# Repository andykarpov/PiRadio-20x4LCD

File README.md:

PiRadio-20x4LCD
=======

Python based internet radio project for RaspberryPi to play internet radio streams and control it using custom atmega328p-based board with 
connected 20x4 character display, rotary encoder, potentiometer, 2xMSGEQ7 board and PT2322 audio processor board.

All hardware-specific EAGLE projects are located under 'schematic' subfolder. 
All required non-standard libraries are available upon request. Some of them are self-made from scratch, some of them googled in the internet.

**Prerequesties:**

1. You should have a working raspberry pi with latest raspbian (at least 2012-12-18)
2. Also we assumes that your network connection (wired or wireless) is also running well
3. Your arduino-based board is connected via internal on-board serial port  
   (assuming arduino/PyRadioInterface sketch is already uploaded there, all external hardware is connected to the arduino - 
   such as rotary encoder, potentiometer, PT2322 board, MSGEQ7 board)
4. You are logged in as user 'pi' with it's default home at /home/pi/ 

**Installation:**

1. sudo apt-get update && sudo apt-get upgrade
2. sudo apt-get install mpd mpc python-serial python-mpd2 git
3. cd && git clone https://github.com/andykarpov/PiRadio-20x4LCD.git PiRadio
4. cd /home/pi/PiRadio
5. sudo ln -s /home/pi/PiRadio/etc/init.d/pi-radio /etc/init.d/pi-radio
6. chmod -R a+rwx data/ 
7. cd /home/pi/PiRadio/init.d/
8. sudo chmod a+x pi-radio
9. sudo nano /etc/mpd - change "localhost" to "any"
10. sudo alsamixer - set a desired output level
11. sudo alsactl store
12. sudo /etc/init.d/pi-radio start
13. sudo update-rc.d pi-radio defaults
14. sudo reboot

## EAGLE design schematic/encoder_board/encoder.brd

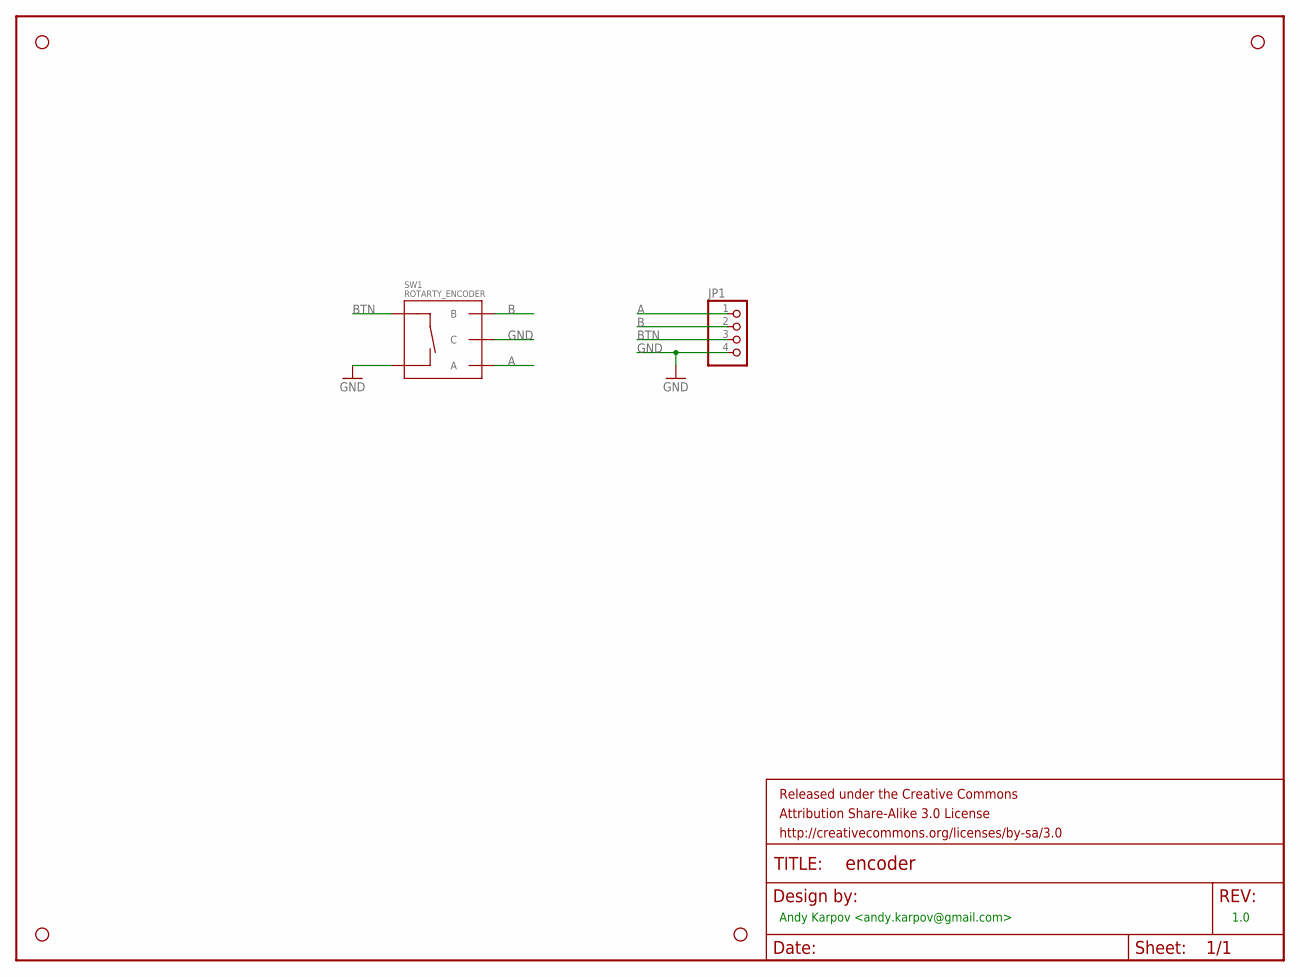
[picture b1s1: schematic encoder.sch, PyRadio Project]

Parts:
FRAME1: FRAME-LETTER; CREATIVE_COMMONS
JP1: PINHD-1X4; 1X04
STANDOFF1, STANDOFF2, STANDOFF3, STANDOFF4: STAND-OFF
SW1: ROTARTY_ENCODER; ROTARY_ENC_PLAIN

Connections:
A: JP1.1, SW1.A
B: JP1.2, SW1.B
BTN: JP1.3, SW1.SW+
GND: JP1.4, SW1.C, SW1.SW-

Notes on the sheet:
Andy Karpov <andy.karpov@gmail.com>
1.0

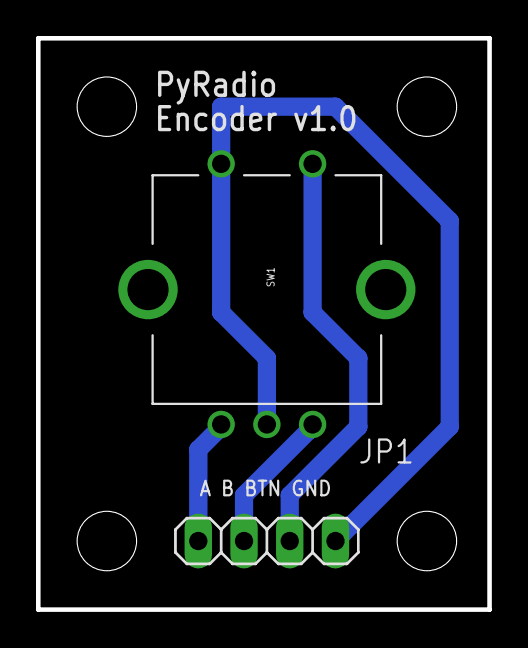
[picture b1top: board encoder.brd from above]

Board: 2 copper layers, 25.1 x 31.7 mm, 7 parts (0 on the bottom side), 4 nets.

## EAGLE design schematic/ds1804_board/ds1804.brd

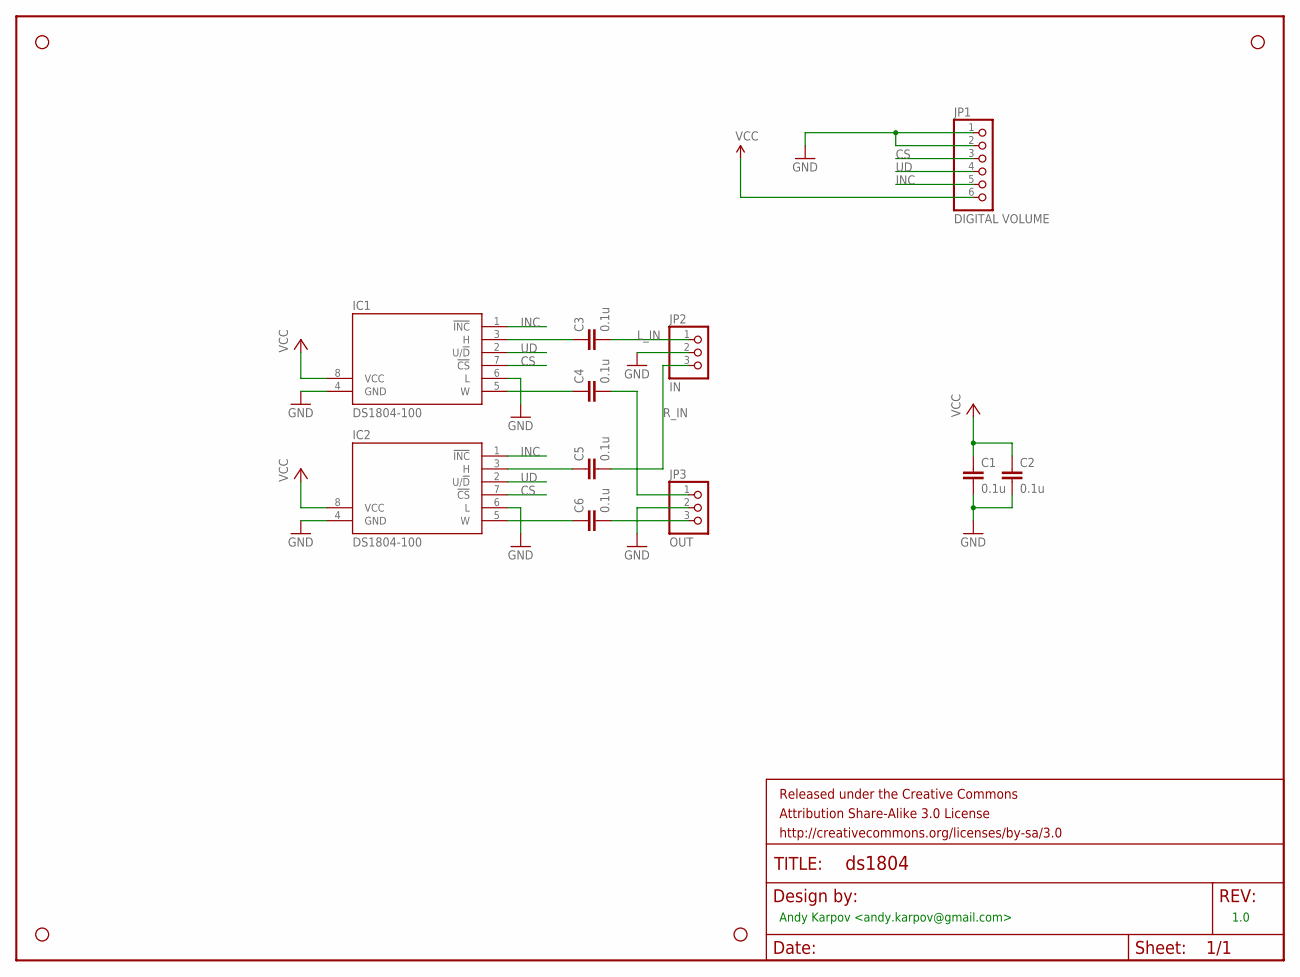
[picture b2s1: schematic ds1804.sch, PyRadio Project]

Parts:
C1, C2, C3, C4, C5, C6: 0.1u; C025-025X050
FRAME1: FRAME-LETTER; CREATIVE_COMMONS
IC1, IC2: DS1804-100; DIL08
JP1: DIGITAL VOLUME; 1X06
JP2: IN; 1X03
JP3: OUT; 1X03
STANDOFF1, STANDOFF2, STANDOFF3, STANDOFF4: STAND-OFF

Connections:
CS: IC1.7 (!CS), IC2.7 (!CS), JP1.3
GND: C1.2, C2.2, IC1.4 (GND), IC1.6 (L), IC2.4 (GND), IC2.6 (L), JP1.1, JP1.2, JP2.2, JP3.2
INC: IC1.1 (!INC), IC2.1 (!INC), JP1.5
L_IN: C3.2, JP2.1
L_OUT: C4.2, JP3.1
unnamed: C5.1, IC2.3 (H)
unnamed: C6.1, IC2.5 (W)
unnamed: C3.1, IC1.3 (H)
unnamed: C4.1, IC1.5 (W)
R_IN: C5.2, JP2.3
R_OUT: C6.2, JP3.3
UD: IC1.2 (U/!D), IC2.2 (U/!D), JP1.4
VCC: C1.1, C2.1, IC1.8 (VCC), IC2.8 (VCC), JP1.6

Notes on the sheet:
Andy Karpov <andy.karpov@gmail.com>
1.0

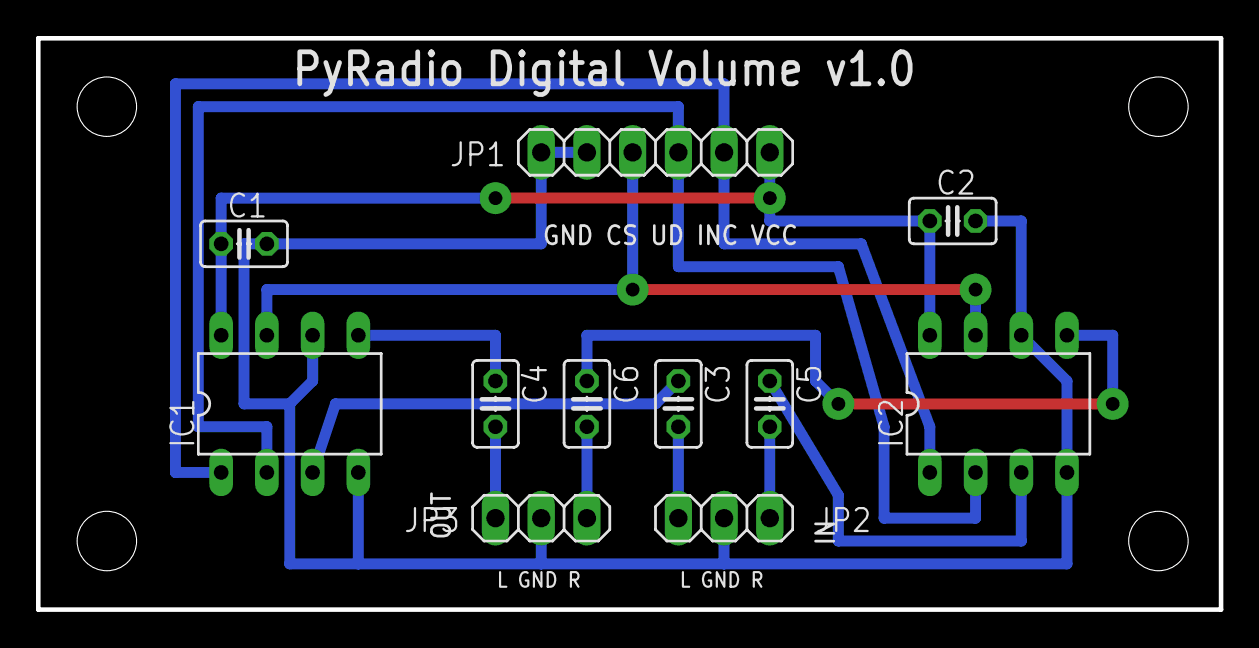
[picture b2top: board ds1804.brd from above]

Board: 2 copper layers, 65.7 x 31.7 mm, 16 parts (0 on the bottom side), 13 nets.

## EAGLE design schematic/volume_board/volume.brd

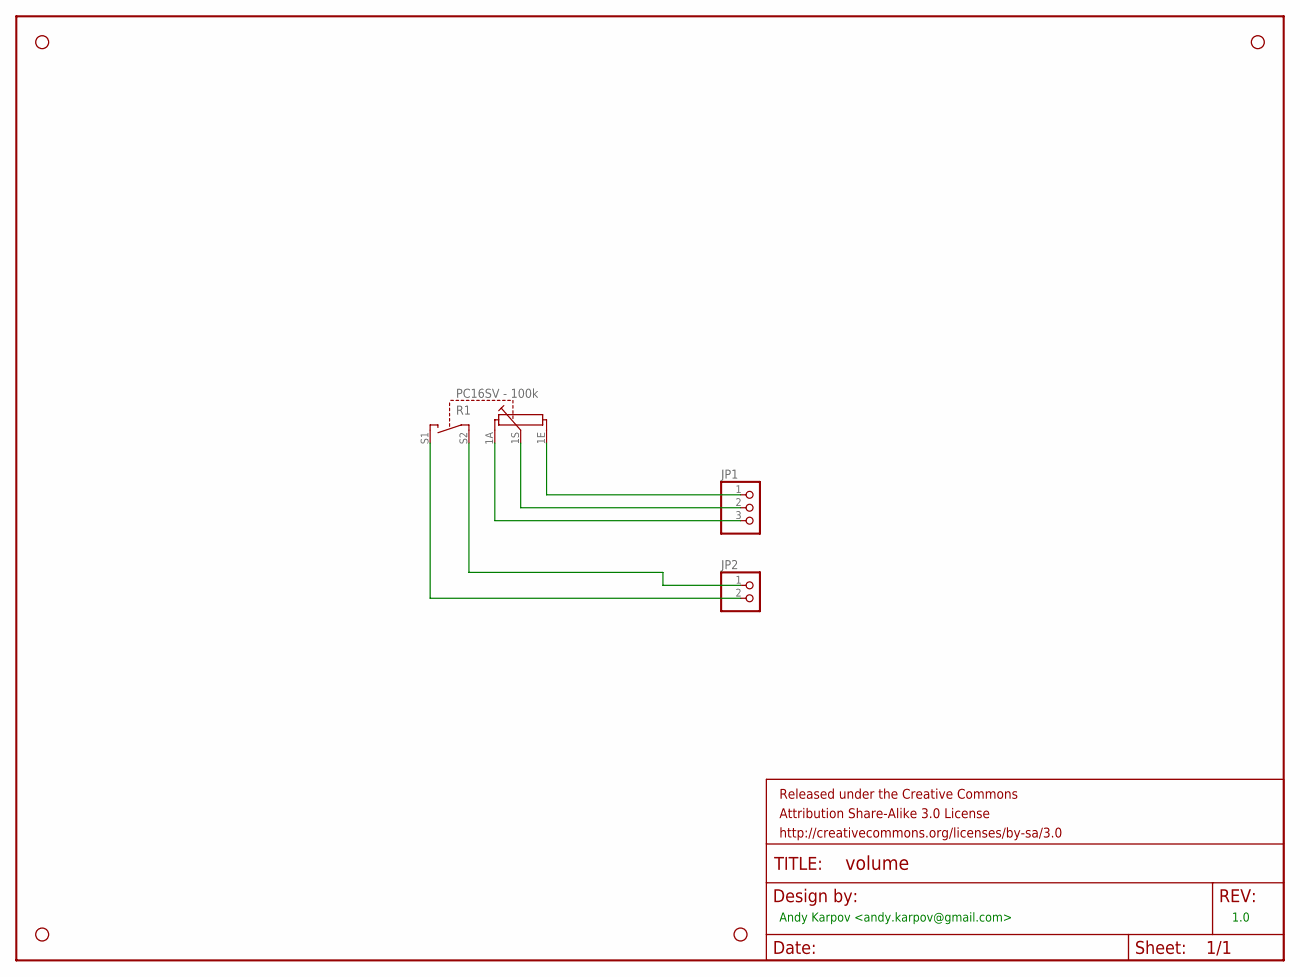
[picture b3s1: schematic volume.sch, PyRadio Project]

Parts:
FRAME1: FRAME-LETTER; CREATIVE_COMMONS
JP1: PINHD-1X3; 1X03
JP2: PINHD-1X2; 1X02
R1: PC16SV - 100k; PC16SV
STANDOFF1, STANDOFF2, STANDOFF3, STANDOFF4: STAND-OFF

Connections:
unnamed: JP1.1, R1.1E
unnamed: JP1.2, R1.1S
unnamed: JP1.3, R1.1A
unnamed: JP2.1, R1.S2
unnamed: JP2.2, R1.S1

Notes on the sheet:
Andy Karpov <andy.karpov@gmail.com>
1.0

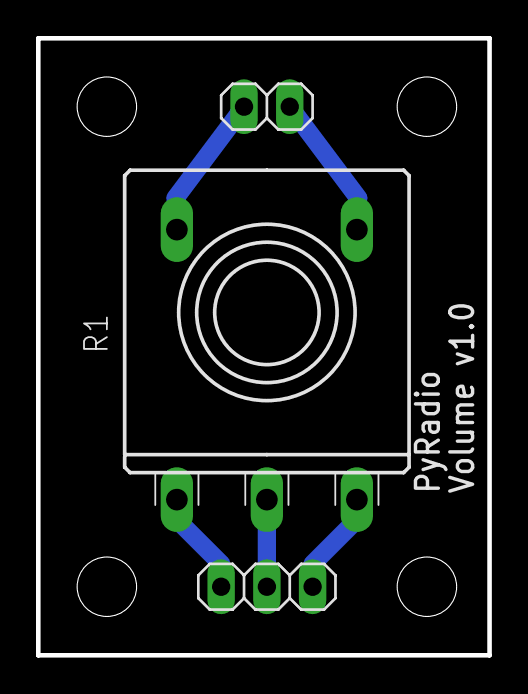
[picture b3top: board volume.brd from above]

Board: 2 copper layers, 25.1 x 34.3 mm, 8 parts (0 on the bottom side), 5 nets.

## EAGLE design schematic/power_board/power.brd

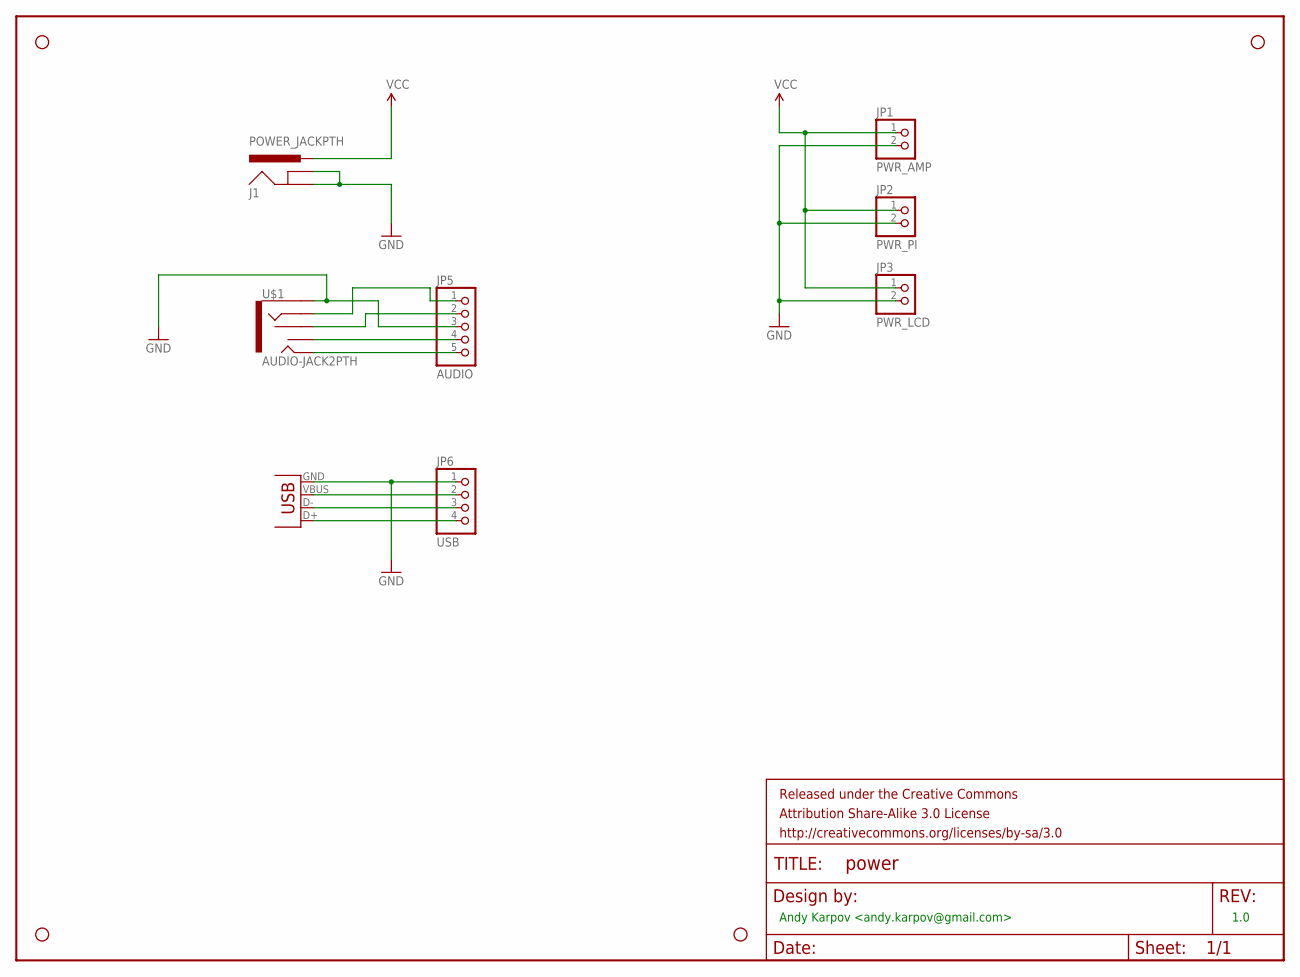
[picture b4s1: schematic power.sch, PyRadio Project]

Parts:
FRAME1: FRAME-LETTER; CREATIVE_COMMONS
J1: POWER_JACKPTH; POWER_JACK_PTH
JP1: PWR_AMP; 1X02
JP2: PWR_PI; 1X02
JP3: PWR_LCD; 1X02
JP4: USB-B; USB-B-PTH
JP5: AUDIO; 1X05
JP6: USB; 1X04
STANDOFF1, STANDOFF2, STANDOFF3, STANDOFF4: STAND-OFF
U$1: AUDIO-JACK2PTH; AUDIO-JACK

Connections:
GND: J1.GND, J1.GNDBREAK, JP1.2, JP2.2, JP3.2, JP4.GND, JP5.3, JP6.1, U$1.SLEEVE
unnamed: JP4.D+, JP6.4
unnamed: JP5.2, U$1.RSH
unnamed: JP5.1, U$1.RING
unnamed: JP4.VBUS, JP6.2
unnamed: JP4.D-, JP6.3
unnamed: JP5.5, U$1.TIP
unnamed: JP5.4, U$1.TSH
VCC: J1.PWR, JP1.1, JP2.1, JP3.1

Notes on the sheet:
Andy Karpov <andy.karpov@gmail.com>
1.0

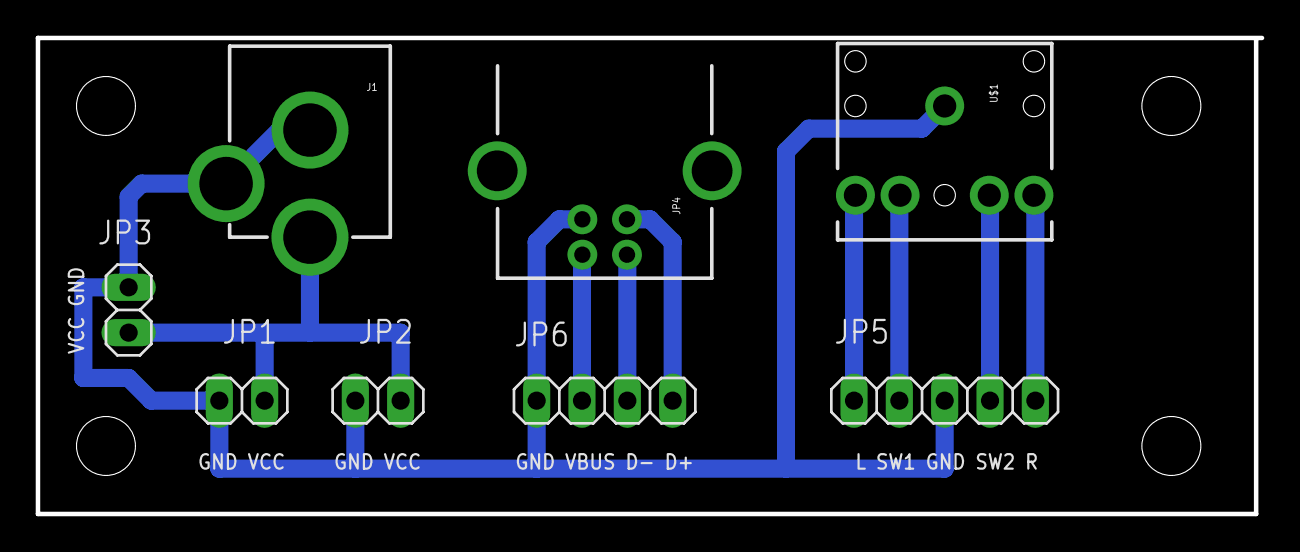
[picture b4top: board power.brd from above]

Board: 2 copper layers, 68.6 x 26.7 mm, 13 parts (0 on the bottom side), 9 nets.

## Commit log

2013-05-16 Moved/splitted 20x4 LCD based code from PyRadio repository

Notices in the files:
parts and their libraries:
SparkFun-Aesthetics: Licensing: CC v3.0 Share-Alike You are welcome to use this library for commercial purposes.
SparkFun-Aesthetics: Released under the Creative Commons Attribution Share-Alike 3.0 License
SparkFun-Aesthetics: http://creativecommons.org/licenses/by-sa/3.0
